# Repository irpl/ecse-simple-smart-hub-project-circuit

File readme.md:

# ECSE Project PCB

for 3d model if the ESP's board doesnt render:
[https://gitlab.com/VictorLamoine/kicad](https://gitlab.com/VictorLamoine/kicad)

## PCB

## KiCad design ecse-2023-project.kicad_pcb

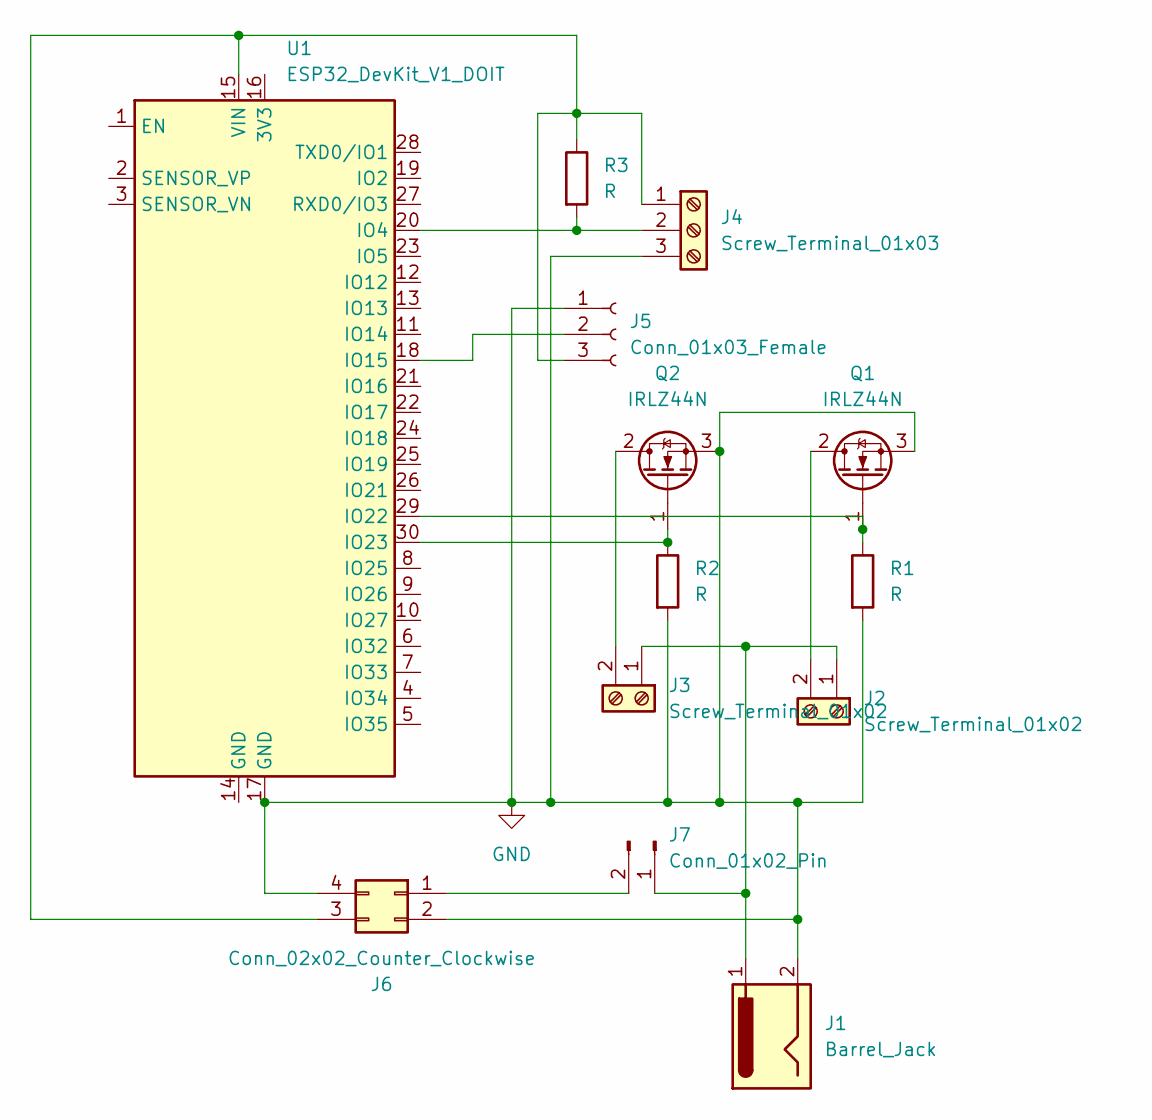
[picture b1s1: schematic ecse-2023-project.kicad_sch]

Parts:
J1: Barrel_Jack; BarrelJack_Horizontal
J2, J3: Screw_Terminal_01x02; TerminalBlock_Phoenix_MKDS-1,5-2_1x02_P5.00mm_Horizontal
J4: Screw_Terminal_01x03; TerminalBlock_Phoenix_MKDS-1,5-3_1x03_P5.00mm_Horizontal
J5: Conn_01x03_Female; PinSocket_1x03_P2.54mm_Vertical
J6: Conn_02x02_Counter_Clockwise; SRT_MPT1584EN_Module
J7: Conn_01x02_Pin; PinHeader_1x02_P2.54mm_Vertical
Q1, Q2: IRLZ44N; TO-220-3_Vertical
R1, R2, R3: R; R_Axial_DIN0207_L6.3mm_D2.5mm_P2.54mm_Vertical
U1: ESP32_DevKit_V1_DOIT; esp32_devkit_v1_doit

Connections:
GND: J1.2, J4.3, J5.1, J6.2, J6.4, Q1.3 (S), Q2.3 (S), R1.2, R2.2, U1.17 (GND)
unnamed: J1.1, J2.1, J3.1, J7.1
unnamed: J2.2, Q1.2 (D)
unnamed: J3.2, Q2.2 (D)
unnamed: J4.1, J5.3, J6.3, R3.1, U1.15 (VIN)
unnamed: J4.2, R3.2, U1.20 (IO4)
unnamed: J5.2, U1.18 (IO15)
unnamed: J6.1, J7.2
unnamed: Q1.1 (G), R1.1, U1.29 (IO22)
unnamed: Q2.1 (G), R2.1, U1.30 (IO23)

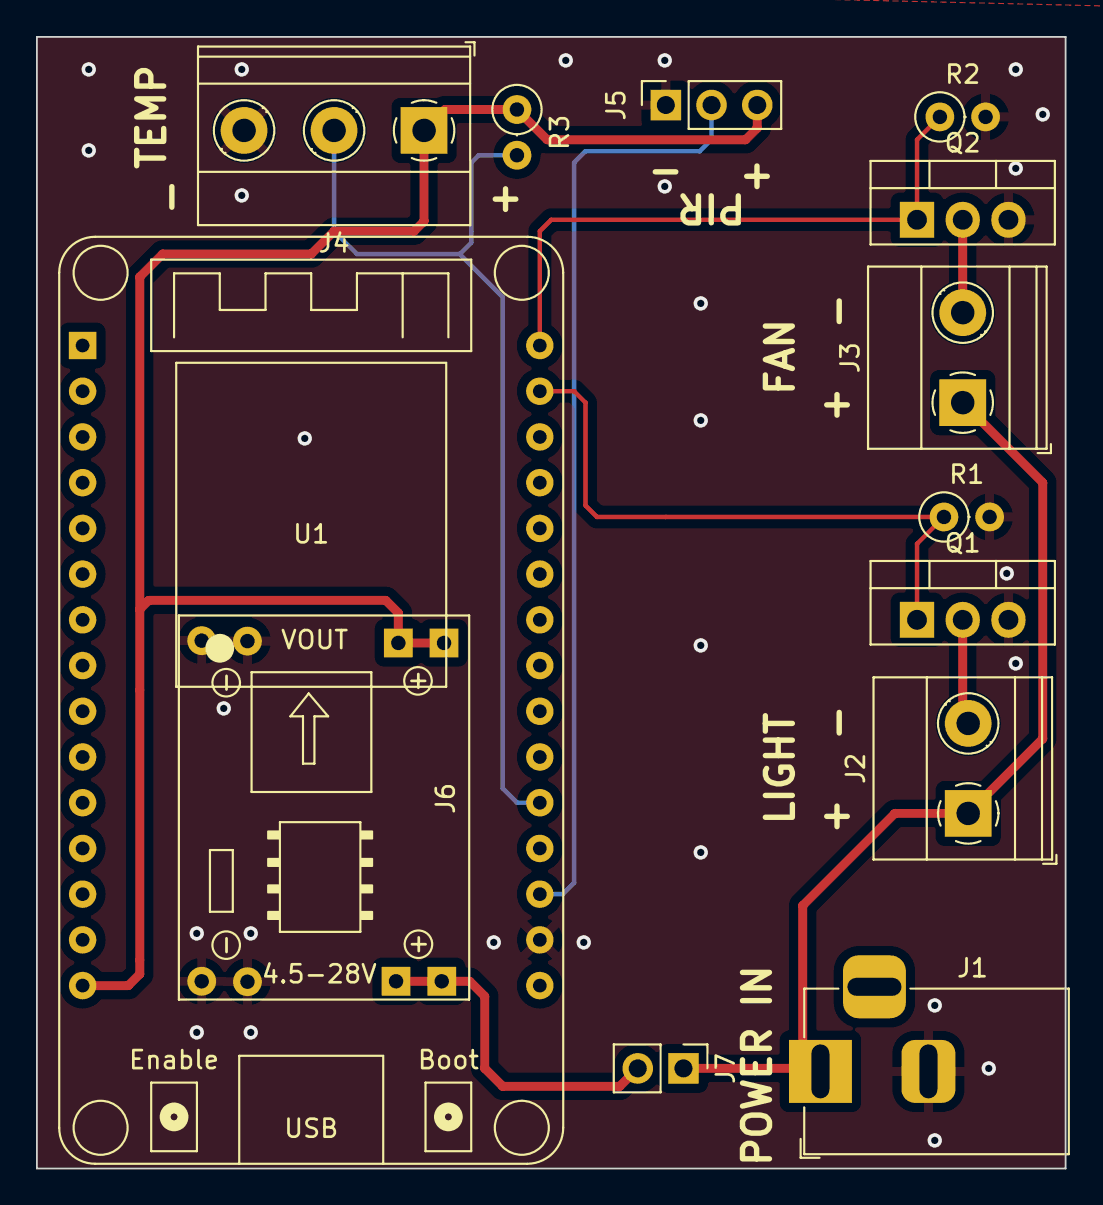
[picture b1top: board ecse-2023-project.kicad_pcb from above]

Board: 2 copper layers, 57.2 x 62.9 mm, 13 parts (0 on the bottom side), 10 nets.

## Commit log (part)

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2024-05-04 replaced screw terminal with barrel jack for the power in port. changed label from 12v to power in. changed pin order for temp port to match label
2024-05-17 added a buck to the pcb so that that prower port can power the esp
2024-06-21 added optional buck converter for esp
2024-06-21 added readme
2024-06-21 made link clickable
2024-06-21 title
2025-03-13 added a gnd component to the sch and a gnd plain to the pcb
2026-05-05 adding image of the pcb with components for stores site
